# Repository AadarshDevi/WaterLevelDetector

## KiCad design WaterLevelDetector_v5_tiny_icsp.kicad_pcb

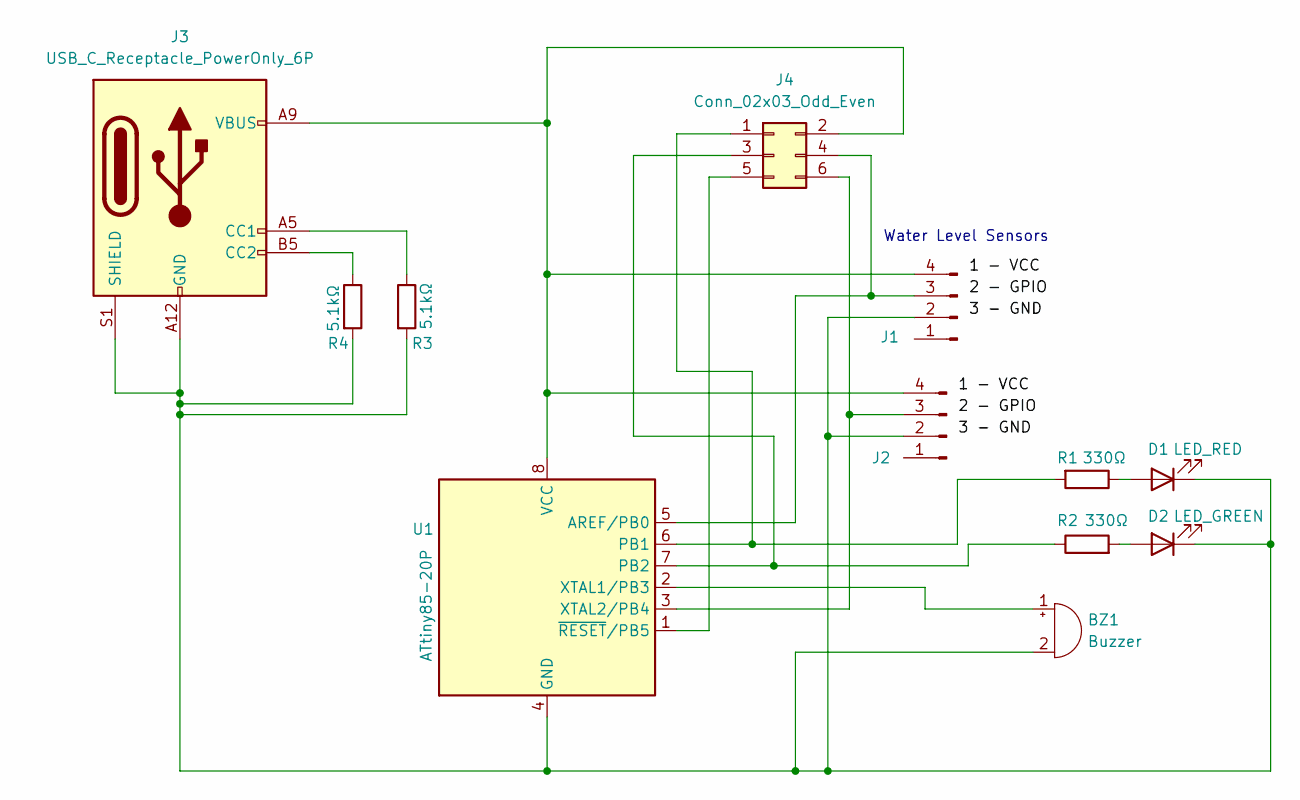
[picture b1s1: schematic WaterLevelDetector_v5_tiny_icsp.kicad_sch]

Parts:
BZ1: Buzzer; Buzzer_12x9.5RM7.6
D1: LED_RED; LED_D5.0mm
D2: LED_GREEN; LED_D5.0mm
J1, J2: PinHeader_1x04_P2.00mm_Horizontal
J3: USB_C_Receptacle_PowerOnly_6P; USB_C_Receptacle_GCT_USB4125-xx-x_6P_TopMnt_Horizontal
J4: Conn_02x03_Odd_Even; PinHeader_2x03_P2.54mm_Vertical
R1, R2: 330Ω; R_Axial_DIN0207_L6.3mm_D2.5mm_P7.62mm_Horizontal
R3, R4: 5.1kΩ; R_Axial_DIN0207_L6.3mm_D2.5mm_P7.62mm_Horizontal
U1: ATtiny85-20P; DIP-8_W7.62mm_Socket

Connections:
unnamed: BZ1.1 (+), U1.2 (XTAL1/PB3)
unnamed: BZ1.2 (-), D1.1 (K), D2.1 (K), J1.2, J2.2, J3.A12 (GND), J3.B12 (GND), J3.S1 (SHIELD), R3.2, R4.2, U1.4 (GND)
unnamed: D1.2 (A), R1.1
unnamed: D2.2 (A), R2.2
unnamed: J1.3, J4.4, U1.5 (AREF/PB0)
unnamed: J1.4, J2.4, J3.A9 (VBUS), J3.B9 (VBUS), J4.2, U1.8 (VCC)
unnamed: J2.3, J4.6, U1.3 (XTAL2/PB4)
unnamed: J3.A5 (CC1), R3.1
unnamed: J3.B5 (CC2), R4.1
unnamed: J4.1, R1.2, U1.6 (PB1)
unnamed: J4.3, R2.1, U1.7 (PB2)
unnamed: J4.5, U1.1 (~RESET/PB5)

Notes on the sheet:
Water Level Sensors

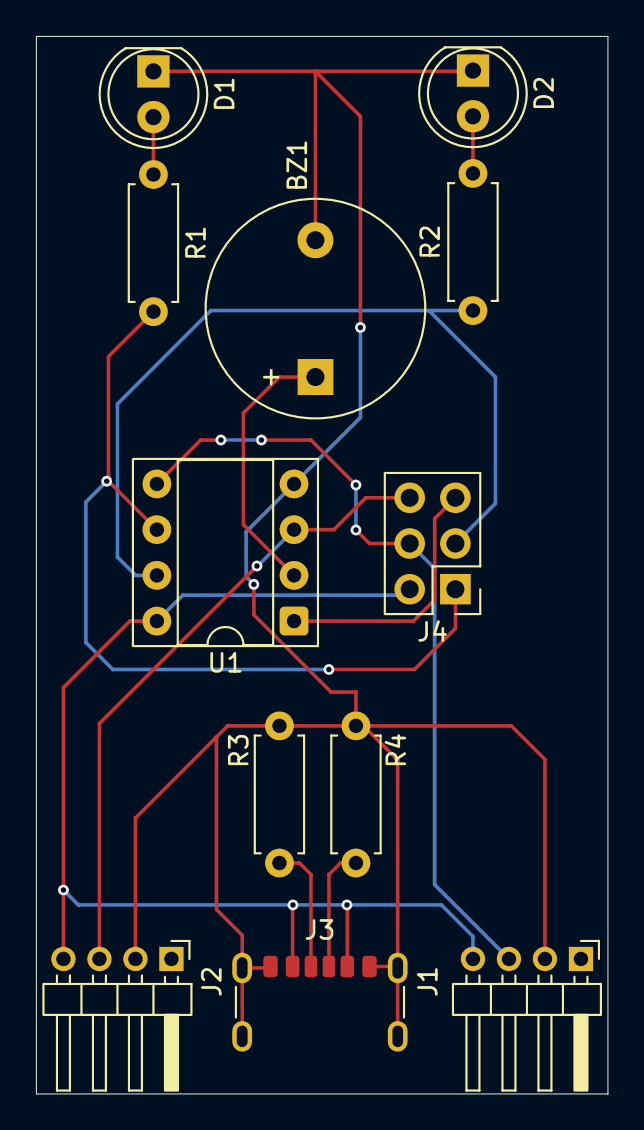
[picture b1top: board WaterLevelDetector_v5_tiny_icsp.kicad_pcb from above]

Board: 2 copper layers, 31.8 x 58.8 mm, 12 parts (0 on the bottom side), 12 nets.

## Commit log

2026-04-07 atmega328p, attiny85, attiny85 ICSP
2026-04-07 some random files
2026-04-07 updated schematics to hold icsp and pcb also has it
2026-04-07 made the pcb area smaller
2026-04-07 made the pcb even more smaller
2026-04-07 hopefully made the leds red and green: schematic update
2026-04-07 hopefully made the leds red and green: pcb update
2026-04-07 something changed
2026-04-11 updated pcb to have gnd gpio vcc
2026-04-11 updated to hold text for vcc and gnd and gpio
